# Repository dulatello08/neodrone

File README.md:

# NeoDrone v1

NeoDrone v1 is a compact all-in-one flight controller + 4-in-1 ESC board for small custom drones.

## Why I made this project

I wanted a cleaner drone stack with fewer separate boards, less wiring, and tighter integration between control and motor drive.  
This project is also a learning build to improve my PCB, embedded, and drone-systems workflow end to end.

## How to use this project

1. Clone this repository.
2. Pull firmware submodule:
   ```bash
   git submodule update --init --recursive
   ```
3. Open the hardware design in KiCad from `hardware/design/neodrone-v1.kicad_pro`.
4. Use firmware from `firmware/` (submodule) or project write-up links below.

Project links:

- [NeoDrone 3D model notes](https://dulatello08.me/blog/neodrone-3d-model/)
- [NeoDrone firmware notes](https://dulatello08.me/blog/neodrone-firmware/)
- [NeoDrone progress log #1](https://dulatello08.me/blog/neodrone-progress-1/)

### Full 3D model screenshot

### PCB screenshot

### Wiring diagram

External wiring used: 4 motors (M1-M4), battery (VBAT/GND), and CRSF receiver (UART + power).

```mermaid
flowchart LR
  Battery["Battery"] --> FC["NeoDrone v1 Board"]
  FC --> M1["Motor 1"]
  FC --> M2["Motor 2"]
  FC --> M3["Motor 3"]
  FC --> M4["Motor 4"]
  CRSF["CRSF Receiver"] --> FC
```

## BOM (truncated)

Full BOM export is in `bom.csv`.  
This is a shortened reference table with links:

| Reference | Part | MPN | Qty | Link |
|---|---|---|---:|---|
| U1 | Main MCU | ATSAMD21G18A-AU | 1 | [Digi-Key](https://www.digikey.com/en/products/result?keywords=ATSAMD21G18A-AU-ND) |
| U3, U5, U6, U7 | 3-phase motor driver | MCF8316A1VRGFR | 4 | [Digi-Key](https://www.digikey.com/en/products/result?keywords=296-MCF8316A1VRGFRCT-ND) |
| U4 | 3.3V regulator | MCP1826S-3302E/DB | 1 | [Digi-Key](https://www.digikey.com/en/products/result?keywords=MCP1826S-3302E%2FDB-ND) |
| U8 | 5V buck regulator | TPS62163DSGT | 1 | [Digi-Key](https://www.digikey.com/en/products/result?keywords=296-30228-1-ND) |
| U9 | IMU | ICM-20602 | 1 | [Digi-Key](https://www.digikey.com/en/products/result?keywords=1428-1060-1-ND) |
| Q1 | P-channel MOSFET | SI7139DP-T1-GE3 | 1 | [Digi-Key](https://www.digikey.com/en/products/result?keywords=SI7139DP-T1-GE3CT-ND) |
| L1-L5 | 2.2uH inductors | SRN2510BTA-2R2M | 5 | [Digi-Key](https://www.digikey.com/en/products/result?keywords=118-SRN2510BTA-2R2MCT-ND) |
| D1 | 12V zener diode | BZT52B12 RHG | 1 | [Digi-Key](https://www.digikey.com/en/products/result?keywords=BZT52B12RHGCT-ND) |
| D2 | TVS diode | SMAJ18A-13-F | 1 | [Digi-Key](https://www.digikey.com/en/products/result?keywords=SMAJ18A-FDICT-ND) |
| C9 | Bulk electrolytic cap | EEE-FP1E331AP | 1 | [Digi-Key](https://www.digikey.com/en/products/result?keywords=PCE4439CT-ND) |

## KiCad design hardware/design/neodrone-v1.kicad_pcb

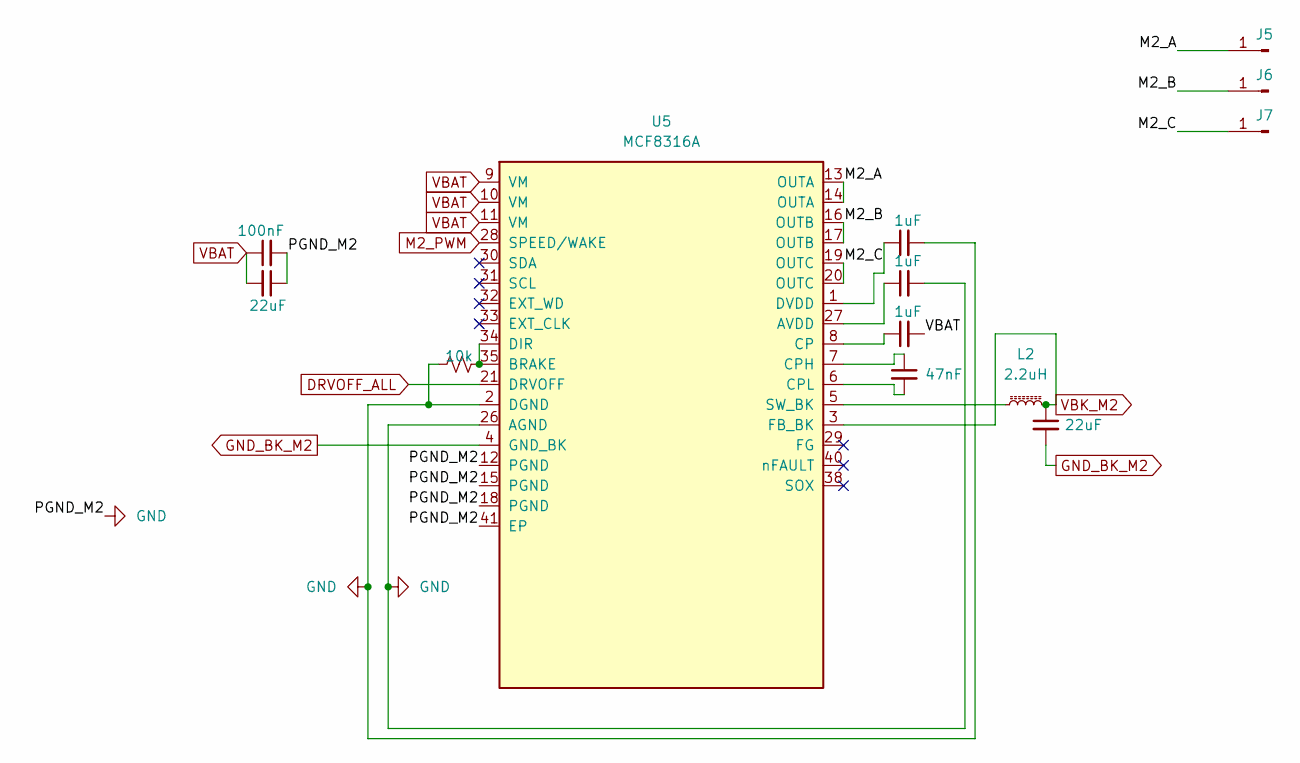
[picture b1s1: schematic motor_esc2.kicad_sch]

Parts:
C21: 100nF; C_0603_1608Metric_Pad1.08x0.95mm_HandSolder
C22, C27: 22uF; C_1206_3216Metric_Pad1.33x1.80mm_HandSolder
C23, C24, C25: 1uF; C_0603_1608Metric_Pad1.08x0.95mm_HandSolder
C26: 47nF; C_0603_1608Metric_Pad1.08x0.95mm_HandSolder
J5, J6, J7: SolderWirePad_1x01_SMD_2x4mm
L2: 2.2uH; L_1008_2520Metric_Pad1.43x2.20mm_HandSolder
R9: 10k; R_0402_1005Metric_Pad0.72x0.64mm_HandSolder
U5: MCF8316A; MCF8316A_RGF0040E_VQFN-40-1EP_7x5mm_P0.5mm_EP5.5x3.5mm

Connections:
/motor_esc2/M2_A: J5.1, U5.13 (OUTA), U5.14 (OUTA)
/motor_esc2/M2_B: J6.1, U5.16 (OUTB), U5.17 (OUTB)
/motor_esc2/M2_C: J7.1, U5.19 (OUTC), U5.20 (OUTC)
DRVOFF_ALL: U5.21 (DRVOFF); also elsewhere on the board
GND: C21.2, C22.1, C23.2, C24.2, C27.2, R9.1, U5.2 (DGND), U5.4 (GND_BK), U5.12 (PGND), U5.15 (PGND), U5.18 (PGND), U5.26 (AGND), U5.41 (EP); also elsewhere on the board
M2_PWM: U5.28 (SPEED/WAKE); also elsewhere on the board
unnamed: C24.1, U5.27 (AVDD)
unnamed: R9.2, U5.34 (DIR), U5.35 (BRAKE)
unnamed: C25.1, U5.8 (CP)
unnamed: C26.1, U5.7 (CPH)
unnamed: C26.2, U5.6 (CPL)
unnamed: C23.1, U5.1 (DVDD)
unnamed: L2.1, U5.5 (SW_BK)
VBAT: C21.1, C22.2, C25.2, U5.9 (VM), U5.10 (VM), U5.11 (VM); also elsewhere on the board
VBK_M2: C27.1, L2.2, U5.3 (FB_BK)

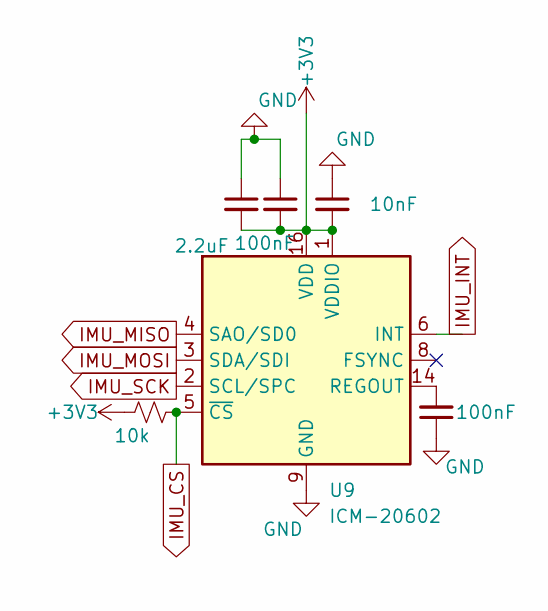
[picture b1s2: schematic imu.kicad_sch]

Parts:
C7, C8: 100nF; C_0603_1608Metric_Pad1.08x0.95mm_HandSolder
C44: 10nF; C_0402_1005Metric_Pad0.74x0.62mm_HandSolder
C45: 2.2uF; C_0603_1608Metric_Pad1.08x0.95mm_HandSolder
R3: 10k; R_0402_1005Metric_Pad0.72x0.64mm_HandSolder
U9: ICM-20602; LGA-16_3x3mm_P0.5mm

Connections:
+3V3: C8.2, C44.2, C45.2, R3.1, U9.1 (VDDIO), U9.16 (VDD); also elsewhere on the board
GND: C7.1, C8.1, C44.1, C45.1, U9.9 (GND), U9.10 (GND), U9.11 (GND), U9.12 (GND), U9.13 (GND), U9.15 (GND); also elsewhere on the board
IMU_CS: R3.2, U9.5 (~CS); also elsewhere on the board
IMU_INT: U9.6 (INT); also elsewhere on the board
IMU_MISO: U9.4 (SAO/SD0); also elsewhere on the board
IMU_MOSI: U9.3 (SDA/SDI); also elsewhere on the board
IMU_SCK: U9.2 (SCL/SPC); also elsewhere on the board
unnamed: C7.2, U9.14 (REGOUT)

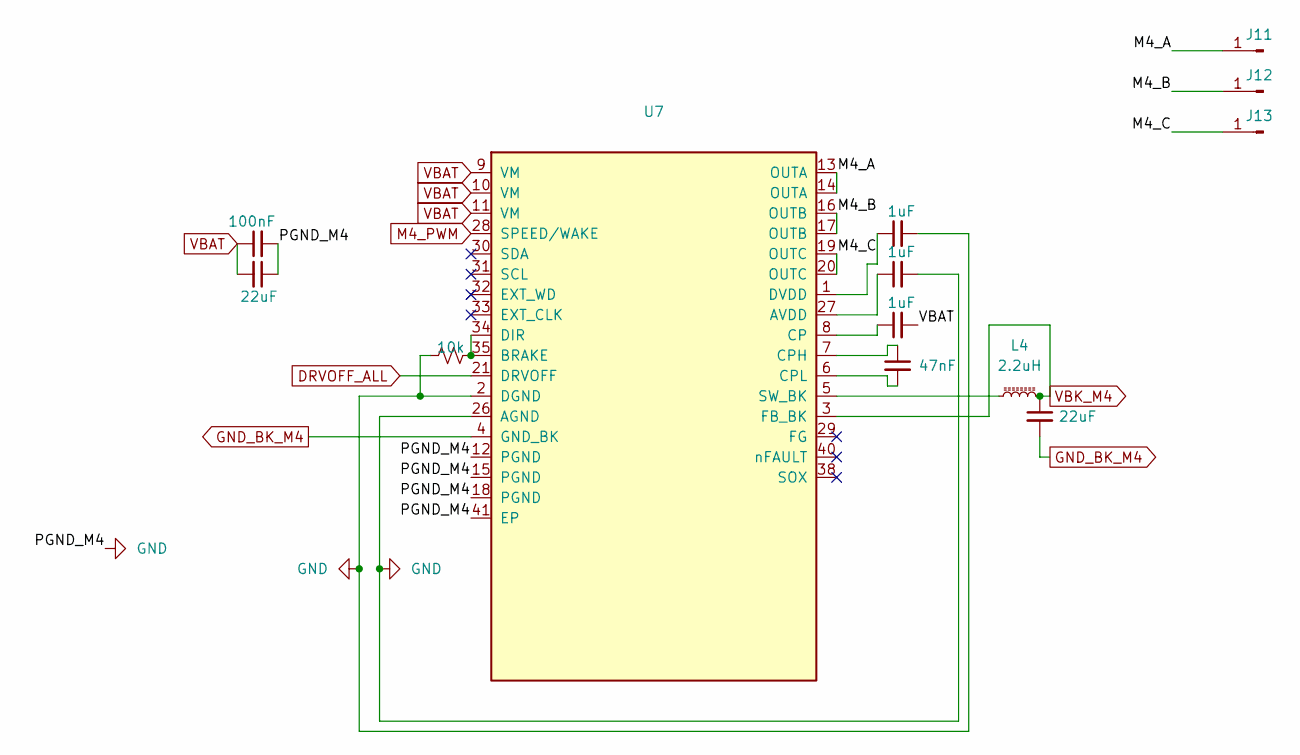
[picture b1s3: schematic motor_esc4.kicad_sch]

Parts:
C35: 100nF; C_0603_1608Metric_Pad1.08x0.95mm_HandSolder
C36, C41: 22uF; C_1206_3216Metric_Pad1.33x1.80mm_HandSolder
C37, C38, C39: 1uF; C_0603_1608Metric_Pad1.08x0.95mm_HandSolder
C40: 47nF; C_0603_1608Metric_Pad1.08x0.95mm_HandSolder
J11, J12, J13: SolderWirePad_1x01_SMD_2x4mm
L4: 2.2uH; L_1008_2520Metric_Pad1.43x2.20mm_HandSolder
R15: 10k; R_0402_1005Metric_Pad0.72x0.64mm_HandSolder
U7: MCF8316A; MCF8316A_RGF0040E_VQFN-40-1EP_7x5mm_P0.5mm_EP5.5x3.5mm

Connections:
/motor_esc4/M4_A: J11.1, U7.13 (OUTA), U7.14 (OUTA)
/motor_esc4/M4_B: J12.1, U7.16 (OUTB), U7.17 (OUTB)
/motor_esc4/M4_C: J13.1, U7.19 (OUTC), U7.20 (OUTC)
DRVOFF_ALL: U7.21 (DRVOFF); also elsewhere on the board
GND: C35.2, C36.1, C37.2, C38.2, C41.2, R15.1, U7.2 (DGND), U7.4 (GND_BK), U7.12 (PGND), U7.15 (PGND), U7.18 (PGND), U7.26 (AGND), U7.41 (EP); also elsewhere on the board
M4_PWM: U7.28 (SPEED/WAKE); also elsewhere on the board
unnamed: C38.1, U7.27 (AVDD)
unnamed: R15.2, U7.34 (DIR), U7.35 (BRAKE)
unnamed: C39.1, U7.8 (CP)
unnamed: C40.1, U7.7 (CPH)
unnamed: C40.2, U7.6 (CPL)
unnamed: C37.1, U7.1 (DVDD)
unnamed: L4.1, U7.5 (SW_BK)
VBAT: C35.1, C36.2, C39.2, U7.9 (VM), U7.10 (VM), U7.11 (VM); also elsewhere on the board
VBK_M4: C41.1, L4.2, U7.3 (FB_BK)

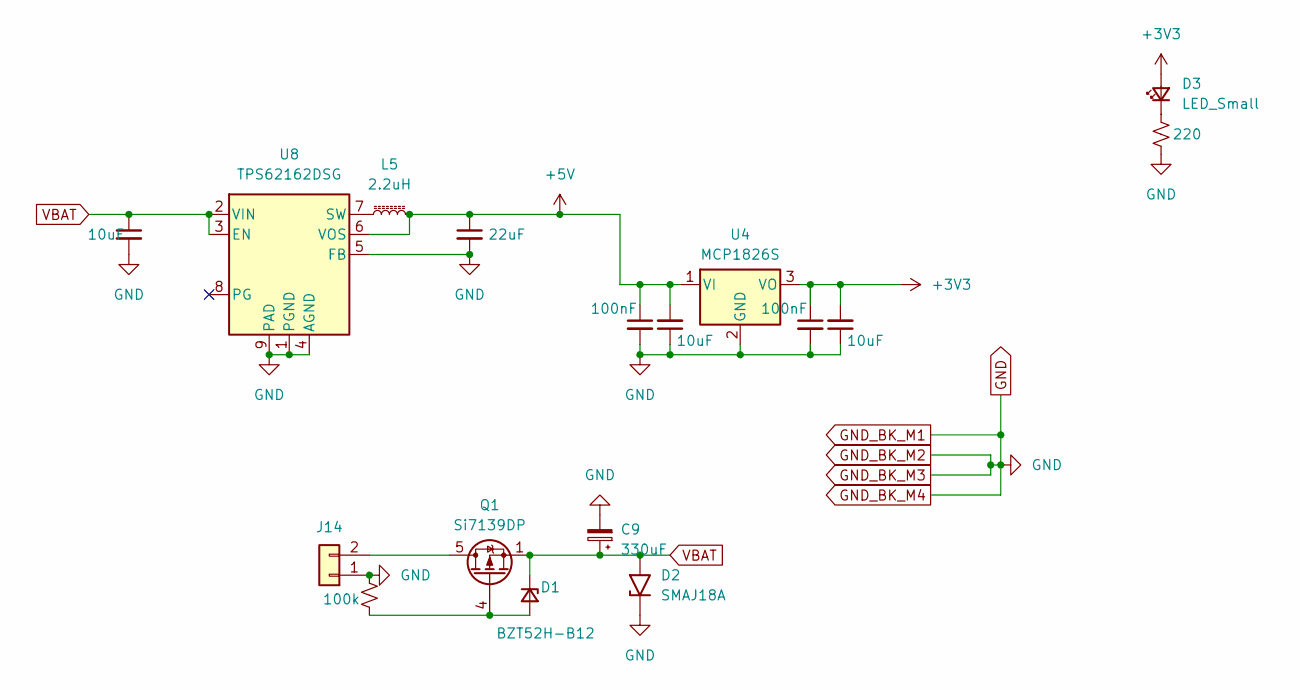
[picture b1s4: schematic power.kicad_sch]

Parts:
C9: 330uF; CP_Elec_10x10.5
C17, C19: 100nF; C_0603_1608Metric_Pad1.08x0.95mm_HandSolder
C18, C20, C42: 10uF; C_0603_1608Metric_Pad1.08x0.95mm_HandSolder
C43: 22uF; C_1206_3216Metric_Pad1.33x1.80mm_HandSolder
D1: BZT52H-B12; D_SOD-123
D2: SMAJ18A; D_SMA_Handsoldering
D3: LED_Small; LED_0402_1005Metric_Pad0.77x0.64mm_HandSolder
J14: Conn_01x02; SolderWire-2sqmm_1x02_P7.8mm_D2mm_OD3.9mm
L5: 2.2uH; L_1008_2520Metric_Pad1.43x2.20mm_HandSolder
Q1: Si7139DP; PowerPAK_SO-8_Single
R6: 220; R_0402_1005Metric_Pad0.72x0.64mm_HandSolder
R17: 100k; R_0402_1005Metric_Pad0.72x0.64mm_HandSolder
U4: MCP1826S; SOT-223-3_TabPin2
U8: TPS62162DSG; WSON-8-1EP_2x2mm_P0.5mm_EP0.9x1.6mm

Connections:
+3V3: C19.1, C20.2, D3.2 (A), U4.3 (VO); also elsewhere on the board
+5V: C17.1, C18.2, C43.1, L5.2, U4.1 (VI), U8.6 (VOS); also elsewhere on the board
GND: C9.2, C17.2, C18.1, C19.2, C20.1, C42.2, C43.2, D2.1 (A1), J14.1, R6.2, R17.2, U4.2 (GND), U8.1 (PGND), U8.4 (AGND), U8.5 (FB), U8.9 (PAD); also elsewhere on the board
unnamed: D1.2 (A), Q1.4 (G), R17.1
unnamed: D3.1 (K), R6.1
unnamed: J14.2, Q1.5 (D)
unnamed: L5.1, U8.7 (SW)
VBAT: C9.1, C42.1, D1.1 (K), D2.2 (A2), Q1.1 (S), Q1.2 (S), Q1.3 (S), U8.2 (VIN), U8.3 (EN); also elsewhere on the board

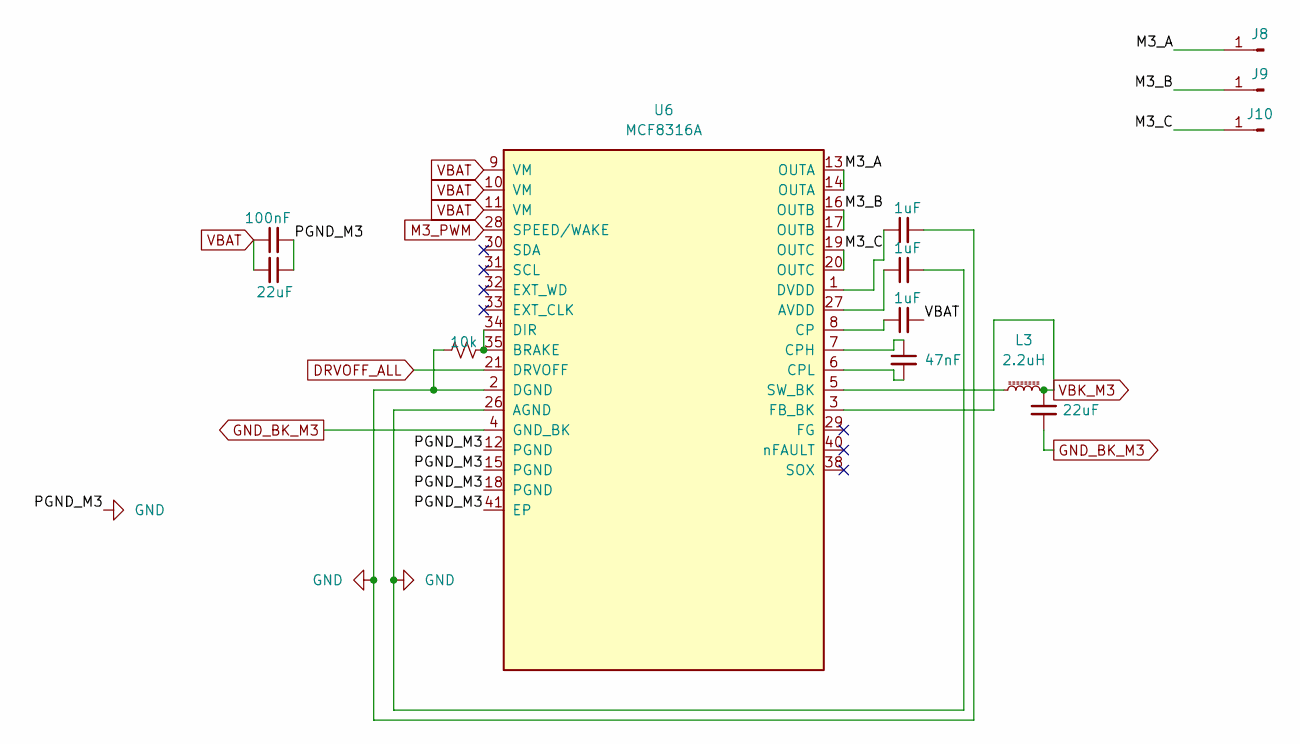
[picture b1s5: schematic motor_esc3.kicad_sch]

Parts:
C28: 100nF; C_0603_1608Metric_Pad1.08x0.95mm_HandSolder
C29, C34: 22uF; C_1206_3216Metric_Pad1.33x1.80mm_HandSolder
C30, C31, C32: 1uF; C_0603_1608Metric_Pad1.08x0.95mm_HandSolder
C33: 47nF; C_0603_1608Metric_Pad1.08x0.95mm_HandSolder
J8, J9, J10: SolderWirePad_1x01_SMD_2x4mm
L3: 2.2uH; L_1008_2520Metric_Pad1.43x2.20mm_HandSolder
R12: 10k; R_0402_1005Metric_Pad0.72x0.64mm_HandSolder
U6: MCF8316A; MCF8316A_RGF0040E_VQFN-40-1EP_7x5mm_P0.5mm_EP5.5x3.5mm

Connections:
/motor_esc3/M3_A: J8.1, U6.13 (OUTA), U6.14 (OUTA)
/motor_esc3/M3_B: J9.1, U6.16 (OUTB), U6.17 (OUTB)
/motor_esc3/M3_C: J10.1, U6.19 (OUTC), U6.20 (OUTC)
DRVOFF_ALL: U6.21 (DRVOFF); also elsewhere on the board
GND: C28.2, C29.1, C30.2, C31.2, C34.2, R12.1, U6.2 (DGND), U6.4 (GND_BK), U6.12 (PGND), U6.15 (PGND), U6.18 (PGND), U6.26 (AGND), U6.41 (EP); also elsewhere on the board
M3_PWM: U6.28 (SPEED/WAKE); also elsewhere on the board
unnamed: C31.1, U6.27 (AVDD)
unnamed: R12.2, U6.34 (DIR), U6.35 (BRAKE)
unnamed: C32.1, U6.8 (CP)
unnamed: C33.1, U6.7 (CPH)
unnamed: C33.2, U6.6 (CPL)
unnamed: C30.1, U6.1 (DVDD)
unnamed: L3.1, U6.5 (SW_BK)
VBAT: C28.1, C29.2, C32.2, U6.9 (VM), U6.10 (VM), U6.11 (VM); also elsewhere on the board
VBK_M3: C34.1, L3.2, U6.3 (FB_BK)

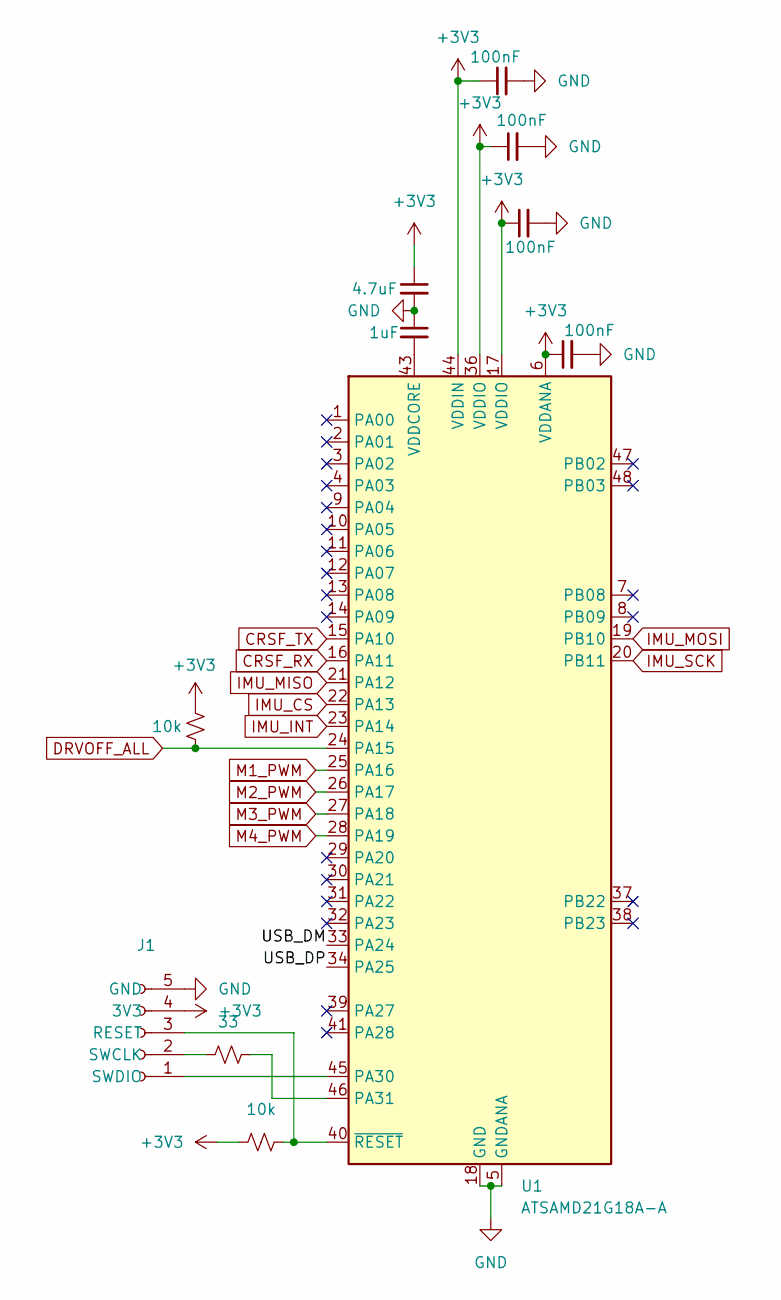
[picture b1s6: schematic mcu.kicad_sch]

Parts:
C1: 1uF; C_0603_1608Metric_Pad1.08x0.95mm_HandSolder
C2, C3, C4, C5: 100nF; C_0603_1608Metric_Pad1.08x0.95mm_HandSolder
C6: 4.7uF; C_0603_1608Metric_Pad1.08x0.95mm_HandSolder
J1: Conn_01x05_Socket; PinSocket_1x05_P1.00mm_Vertical_SMD_Pin1Left
R1, R4: 10k; R_0402_1005Metric_Pad0.72x0.64mm_HandSolder
R2: 33; R_0402_1005Metric_Pad0.72x0.64mm_HandSolder
U1: ATSAMD21G18A-A; TQFP-48_7x7mm_P0.5mm

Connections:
+3V3: C2.1, C3.1, C4.1, C5.1, C6.1, J1.4 (3V3), R1.1, R4.2, U1.6 (VDDANA), U1.17 (VDDIO), U1.36 (VDDIO), U1.44 (VDDIN); also elsewhere on the board
/mcu/USB_DM: U1.33 (PA24)
/mcu/USB_DP: U1.34 (PA25)
CRSF_RX: U1.16 (PA11); also elsewhere on the board
CRSF_TX: U1.15 (PA10); also elsewhere on the board
DRVOFF_ALL: R4.1, U1.24 (PA15); also elsewhere on the board
GND: C1.1, C2.2, C3.2, C4.2, C5.2, C6.2, J1.5 (GND), U1.5 (GNDANA), U1.18 (GND), U1.35 (GND), U1.42 (GND); also elsewhere on the board
IMU_CS: U1.22 (PA13); also elsewhere on the board
IMU_INT: U1.23 (PA14); also elsewhere on the board
IMU_MISO: U1.21 (PA12); also elsewhere on the board
IMU_MOSI: U1.19 (PB10); also elsewhere on the board
IMU_SCK: U1.20 (PB11); also elsewhere on the board
M1_PWM: U1.25 (PA16); also elsewhere on the board
M2_PWM: U1.26 (PA17); also elsewhere on the board
M3_PWM: U1.27 (PA18); also elsewhere on the board
M4_PWM: U1.28 (PA19); also elsewhere on the board
unnamed: J1.3 (RESET), R1.2, U1.40 (~RESET)
unnamed: J1.2 (SWCLK), R2.1
unnamed: J1.1 (SWDIO), U1.45 (PA30)
unnamed: R2.2, U1.46 (PA31)
unnamed: C1.2, U1.43 (VDDCORE)

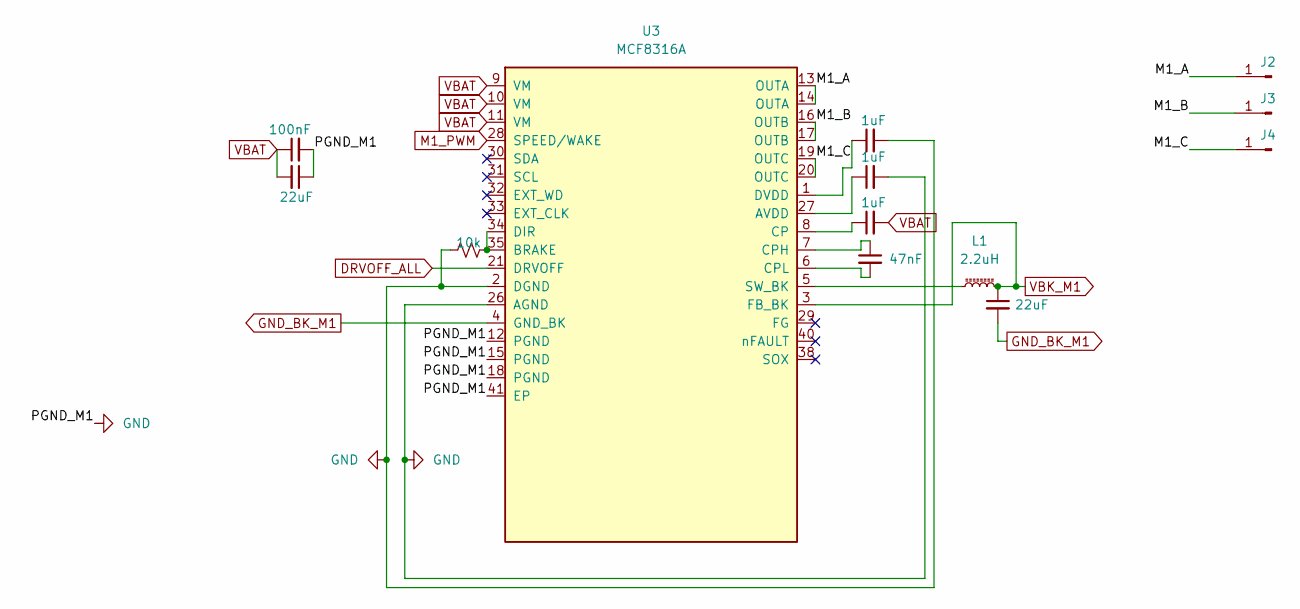
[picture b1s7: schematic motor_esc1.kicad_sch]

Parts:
C10, C16: 22uF; C_1206_3216Metric_Pad1.33x1.80mm_HandSolder
C11: 100nF; C_0603_1608Metric_Pad1.08x0.95mm_HandSolder
C12: 47nF; C_0603_1608Metric_Pad1.08x0.95mm_HandSolder
C13, C14, C15: 1uF; C_0603_1608Metric_Pad1.08x0.95mm_HandSolder
J2, J3, J4: SolderWirePad_1x01_SMD_2x4mm
L1: 2.2uH; L_1008_2520Metric_Pad1.43x2.20mm_HandSolder
R5: 10k; R_0402_1005Metric_Pad0.72x0.64mm_HandSolder
U3: MCF8316A; MCF8316A_RGF0040E_VQFN-40-1EP_7x5mm_P0.5mm_EP5.5x3.5mm

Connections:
/motor_esc1/M1_A: J2.1, U3.13 (OUTA), U3.14 (OUTA)
/motor_esc1/M1_B: J3.1, U3.16 (OUTB), U3.17 (OUTB)
/motor_esc1/M1_C: J4.1, U3.19 (OUTC), U3.20 (OUTC)
DRVOFF_ALL: U3.21 (DRVOFF); also elsewhere on the board
GND: C10.1, C11.2, C14.2, C15.2, C16.2, R5.1, U3.2 (DGND), U3.4 (GND_BK), U3.12 (PGND), U3.15 (PGND), U3.18 (PGND), U3.26 (AGND), U3.41 (EP); also elsewhere on the board
M1_PWM: U3.28 (SPEED/WAKE); also elsewhere on the board
unnamed: C14.1, U3.27 (AVDD)
unnamed: R5.2, U3.34 (DIR), U3.35 (BRAKE)
unnamed: C13.1, U3.8 (CP)
unnamed: C12.1, U3.7 (CPH)
unnamed: C12.2, U3.6 (CPL)
unnamed: C15.1, U3.1 (DVDD)
unnamed: L1.1, U3.5 (SW_BK)
VBAT: C10.2, C11.1, C13.2, U3.9 (VM), U3.10 (VM), U3.11 (VM); also elsewhere on the board
VBK_M1: C16.1, L1.2, U3.3 (FB_BK)

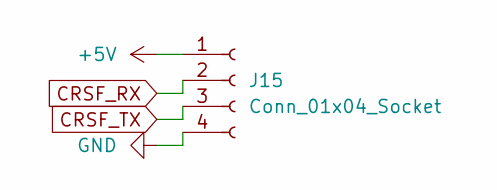
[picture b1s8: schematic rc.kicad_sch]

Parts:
J15: Conn_01x04_Socket; PinSocket_1x04_P1.00mm_Vertical_SMD_Pin1Left

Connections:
+5V: J15.1; also elsewhere on the board
CRSF_RX: J15.2; also elsewhere on the board
CRSF_TX: J15.3; also elsewhere on the board
GND: J15.4; also elsewhere on the board

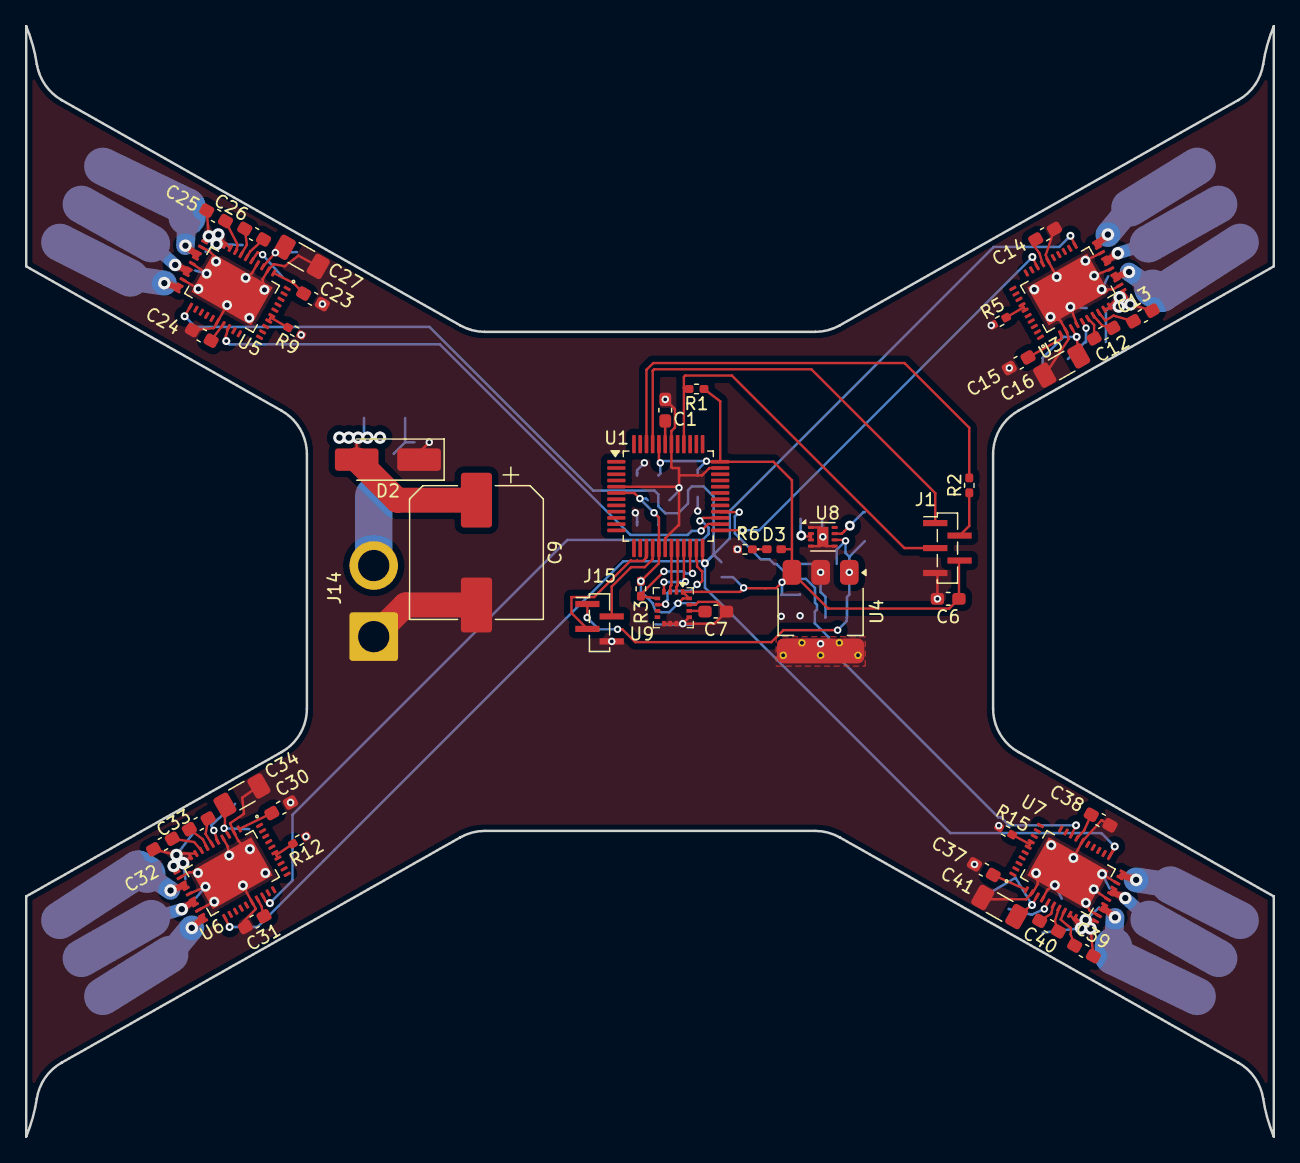
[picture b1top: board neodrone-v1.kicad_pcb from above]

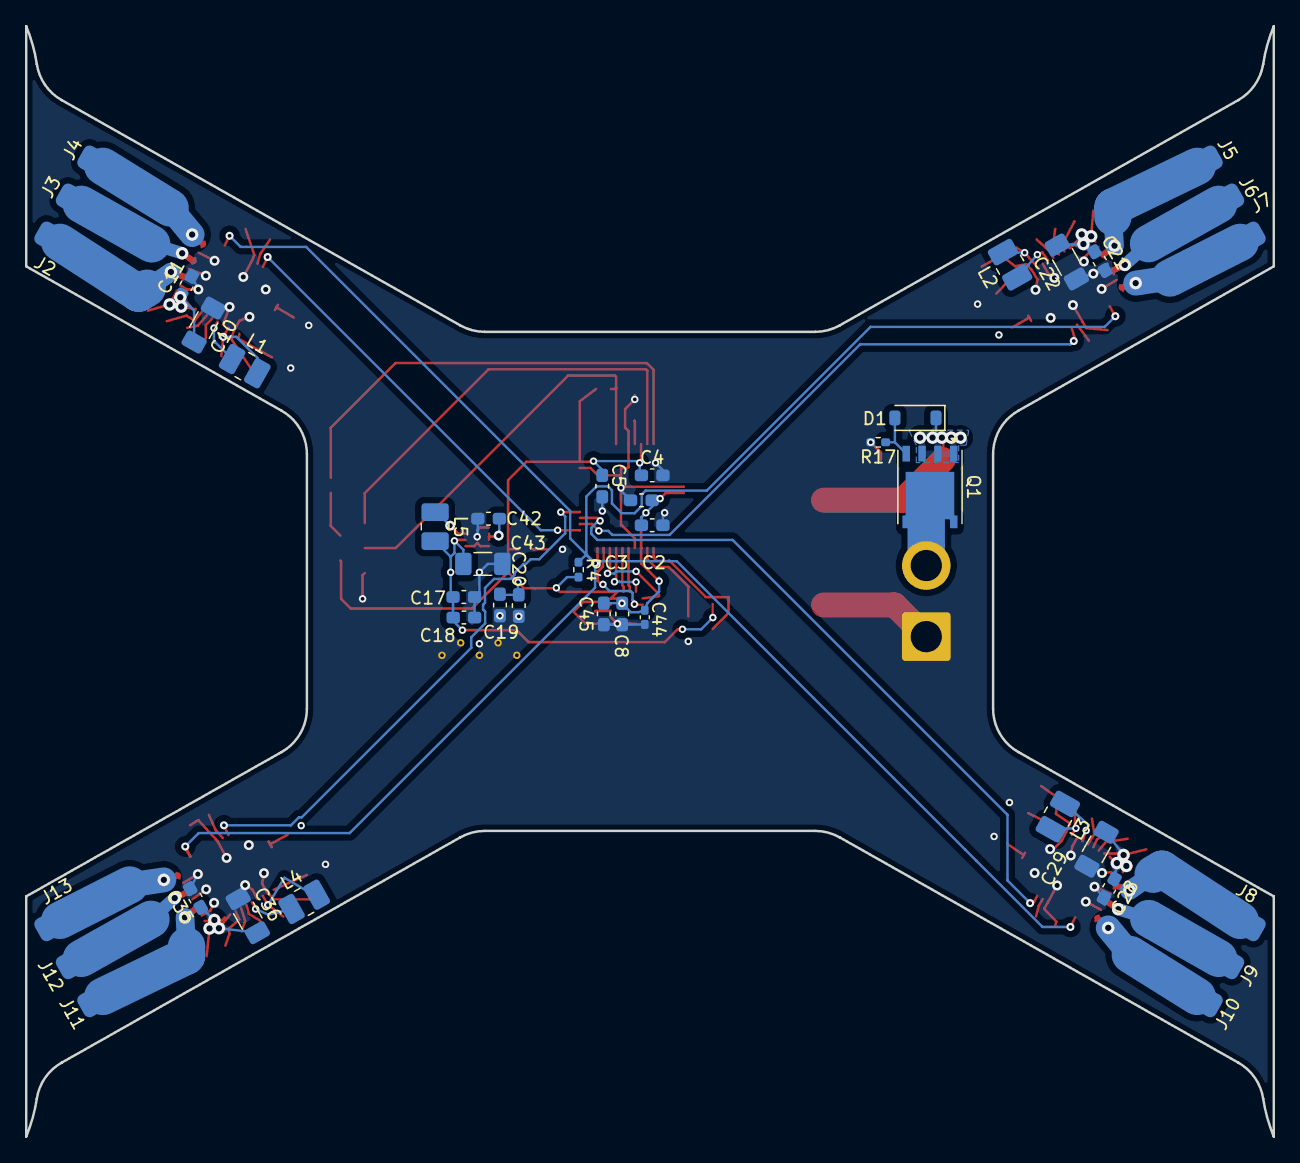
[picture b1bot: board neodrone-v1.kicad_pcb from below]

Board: 4 copper layers, 100.0 x 89.0 mm, 87 parts (42 on the bottom side), 70 nets.

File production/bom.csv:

Designator,Footprint,Quantity,Value,LCSC Part #
"C1, C13, C14, C15, C23, C24, C25, C30, C31, C32, C37, C38, C39",0603,13,1uF,
"C10, C16, C22, C27, C29, C34, C36, C41, C43",1206,9,22uF,
"C11, C17, C19, C2, C21, C28, C3, C35, C4, C5, C7, C8",0603,12,100nF,
"C12, C26, C33, C40",0603,4,47nF,
"C18, C20, C42",0603,3,10uF,
C44,0603,1,10nF,
C45,0603,1,2.2uF,
C6,0603,1,4.7uF,
C9,CP_Elec_10x10.5,1,330uF,
D1,D_SOD-123,1,BZT52H-B12,
D2,D_SMA_Handsoldering,1,SMAJ18A,
D3,0402,1,LED_Small,
J1,PinSocket_1x05_P1.00mm_Vertical_SMD_Pin1Left,1,Conn_01x05_Socket,
J14,SolderWire-2sqmm_1x02_P7.8mm_D2mm_OD3.9mm,1,Conn_01x02,
J15,PinSocket_1x04_P1.00mm_Vertical_SMD_Pin1Left,1,Conn_01x04_Socket,
"L1, L2, L3, L4, L5",1008,5,2.2uH,
Q1,PowerPAK_SO-8_Single,1,Si7139DP,
"R1, R12, R15, R3, R4, R5, R9",0402,7,10k,
R17,0402,1,100k,
R2,0402,1,33,
R6,0402,1,220,
U1,TQFP-48_7x7mm_P0.5mm,1,ATSAMD21G18A-A,
"U3, U5, U6, U7",MCF8316A_RGF0040E_VQFN-40-1EP_7x5mm_P0.5mm_EP5.5x3.5mm,4,MCF8316A,
U4,SOT-223-3_TabPin2,1,MCP1826S,
U8,WSON-8-1EP_2x2mm_P0.5mm_EP0.9x1.6mm,1,TPS62162DSG,
U9,LGA-16_3x3mm_P0.5mm,1,ICM-20602,

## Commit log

2025-12-28 push files
2025-12-28 push files #1
2025-12-28 push files #2 sigh
2025-12-29 imu, motor esc schematics
2025-12-29 more esc schematics, refactoring, root schematic edits
2025-12-29 Schematics mostly done, netclasses, coords for esc (angled)
2026-01-08 A LOT of changes, current state is 2 of 4 ESCs routed, power revamped. \n Board almost done
2026-01-08 A LOT of changes, current state is 2 of 4 ESCs routed, power revamped. #2 \n Board almost done
2026-01-15 done?
2026-01-16 done
2026-01-16 done #2
2026-02-09 Remove obsolete files: deleted positions.csv, and lock files for PCB and schematic
